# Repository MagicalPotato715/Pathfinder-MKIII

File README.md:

****PATHFINDER: MARK III****

-----

About: This is the PCB for the third generation of my project, Pathfinder. The goal for Pathfinder is to make a hexapod walking robot that is able to traverse in diverse and rugged terrain where conventional vehicles (e.g., cars, rovers) prove inefficient. The third generation of Pathfinder (Mark III) will feature significant upgrades from its predecessor (Mark II), including improved motors for speed and weight-bearing, an onboard 7.4V LiPo battery for tetherless power, an accelerometer, and an NRF chip for wireless communication.

Why: I began Pathfinder after my physics teacher encouraged me to join my school's science fair. I had always had an idea for a spider robot that I kept at the back of my mind, but this pushed me to bring it to life. Over the next few weeks, I poured hours every day into learning more about mechanical and electrical engineering. I also sought mentorship from the UC Berkeley Engineering Department and got connected with a Mech E & EECS graduate student.  Mark I of Pathfinder, a simple prototype/proof of concept, was churned out after 2 weeks, just in time for my district's science fair to win me 2nd place. Mark II was developed a few weeks later for the regional science fair. Mark III, the model this PCB is for, will be the culmination of my work over an entire year to be entered into next season's science fair.

(Note: The CAD model was created and fine-tuned over the course 3+ months that were before Highway began, so I didn't record the process in the journals.)

---

**In Depth: How It Works** (for all yall nerds out there)

- **PCB**
  - The PCB is, in essence, a servo driver. It is supposed to be placed on top of a Nucleo F446RE board, taking advantage of its Morpho pins that expose the MCU. The power comes in from a 7.4V 2S LiPo battery connected to the onboard XT60 (just a connector).
  - **Servos** Since the potential ampage could go up to ~10-15A, a pour is used to connect the battery to the 3 buck converters. Each buck converter steps down the battery power from 7.4V to 6V at 5A for 6 servos (two legs). This connection from the buck converters to the servo rails is led by another set of pours. The servos receive PWM input from 15 pins on the right morpho pins and 3 on the left.
  - **Power** The VIN from the XT60 is also connected to the F446RE's onboard VIN pin (it already has a regulator to step down to 3.3V). This power then comes out of the 3.3V pin and is fed to the NRF Chip and the Accelerometer.
  - **Accelerometer** The accelerometer used is the BNO055, an "INTELLIGENT ABSOLUTE ORIENTATION SENSOR, 9-AXIS SENSOR FUSION" (aka gyroscope & accelerometer and prob 9 other things). The BNO055 uses I2C and is connected to SDA & SCL. There is also a manual reset button connected to RST on the BNO055 just for funsies.
  - **NRF Chip** This is going to be used to communicate with the hand-held controller (to be made later). The NRF Chip is the NRF24L01_Breakout. NRF24L01_Breakout uses SPI and thus the MISO, MOSI, CSN, SCK, and CE pins on the F446RE (used on the left morpho pins).
  
- **Body**
  In-depth desc WIP
---

|Component|Quantity|Model|Lowest Price|Link|
|---|---|---|---|---|
|LED|2|VLMR233T2V2-GS08|$0.35|[Link](https://www.aliexpress.com/item/1005008128628087.html?spm=a2g0o.productlist.main.1.3248724bxQyiaJ&algo_pvid=fe447d84-fd13-4e27-8b43-c86227a91054&algo_exp_id=fe447d84-fd13-4e27-8b43-c86227a91054-0&pdp_ext_f=%7B%22order%22%3A%22-1%22%2C%22eval%22%3A%221%22%7D&pdp_npi=4%40dis%21USD%210.35%210.35%21%21%212.50%212.50%21%40212e520f17525897623118806eb6dd%2112000043902875398%21sea%21TW%216187826129%21ABX&curPageLogUid=l7TbgfaGIsM2&utparam-url=scene%3Asearch%7Cquery_from%3A)|
|Button|2 (1x20pcs)|TL1240NQ1JBLK|$1.27|[Link](https://www.aliexpress.com/item/1005003938985112.html?spm=a2g0o.productlist.main.1.4ec72c6f97uelG&algo_pvid=776e63b0-ad1a-4770-b3bd-8e8a47c59f00&algo_exp_id=776e63b0-ad1a-4770-b3bd-8e8a47c59f00-0&pdp_ext_f=%7B%22order%22%3A%22467%22%2C%22eval%22%3A%221%22%7D&pdp_npi=4%40dis%21USD%212.54%211.27%21%21%212.54%211.27%21%402140f54217525901711175058e53bd%2112000027515313621%21sea%21TW%216187826129%21ABX&curPageLogUid=cPSFccWMC2Xx&utparam-url=scene%3Asearch%7Cquery_from%3A)|
|Servo Motor|18 (2x10pcs)|MG996R|$30.81|[Link](https://www.aliexpress.com/item/1005007032811340.html?spm=a2g0o.productlist.main.1.723942Xa42Xahr&algo_pvid=9b9e645d-9469-4d2a-b561-26204b6bf4cc&algo_exp_id=9b9e645d-9469-4d2a-b561-26204b6bf4cc-0&pdp_ext_f=%7B%22order%22%3A%22876%22%2C%22eval%22%3A%221%22%7D&pdp_npi=4%40dis%21TWD%21150.51%21105.30%21%21%214.96%213.47%21%40212a70c017525889078702858e6fc3%2112000039159590615%21sea%21TW%216187826129%21ABX&curPageLogUid=3yZqtCc75vJ0&utparam-url=scene%3Asearch%7Cquery_from%3A#nav-review)|
|10uF Capacitor|7 (1x100pcs)|0805W106K250CC|$0.6|[Link](https://www.aliexpress.com/item/1626652703.html?spm=a2g0o.productlist.main.1.48fb6316RMeZBk&algo_pvid=e693861e-0391-4f51-8de6-32cd16f941e8&algo_exp_id=e693861e-0391-4f51-8de6-32cd16f941e8-0&pdp_ext_f=%7B%22order%22%3A%22290%22%2C%22eval%22%3A%221%22%7D&pdp_npi=4%40dis%21USD%210.60%210.60%21%21%210.60%210.60%21%402102f22c17525900041745529e7ed1%2165044401121%21sea%21TW%216187826129%21ABX&curPageLogUid=cULtsx9Twjzu&utparam-url=scene%3Asearch%7Cquery_from%3A)|
|10k Resistor|5 (1x100pcs)|CR0805-JW-103ELF|$0.35|[Link](https://www.aliexpress.com/item/1005006269805332.html?spm=a2g0o.productlist.main.1.31e33be6PMcjLK&algo_pvid=54fac39b-245b-4873-a9c8-e36e2fd5a510&algo_exp_id=54fac39b-245b-4873-a9c8-e36e2fd5a510-0&pdp_ext_f=%7B%22order%22%3A%22883%22%2C%22eval%22%3A%221%22%7D&pdp_npi=4%40dis%21USD%210.46%210.35%21%21%213.30%212.51%21%40212e532617525903439675817ef045%2112000036544486825%21sea%21TW%216187826129%21ABX&curPageLogUid=AMuzMQYTT7uu&utparam-url=scene%3Asearch%7Cquery_from%3A)|
|500 Resistor|2 (1x100pcs)|CR0805-FX-4990ELF|$0.35|[Link](https://www.aliexpress.com/item/1005006269805332.html?spm=a2g0o.productlist.main.2.1d257f6fZB1phL&aem_p4p_detail=202507150740589457957524426840000094648&algo_pvid=39ad91cb-3682-4b56-ba16-048ebdbe6b9a&algo_exp_id=39ad91cb-3682-4b56-ba16-048ebdbe6b9a-1&pdp_ext_f=%7B%22order%22%3A%22883%22%2C%22eval%22%3A%221%22%7D&pdp_npi=4%40dis%21USD%210.46%210.35%21%21%213.30%212.51%21%402102f0c917525904583394282ef078%2112000036544486825%21sea%21TW%216187826129%21ABX&curPageLogUid=TxMcy0VHgfnU&utparam-url=scene%3Asearch%7Cquery_from%3A&search_p4p_id=202507150740589457957524426840000094648_1)|
|NRF Board|1|NRF24L01_Breakout|$0.58|[Link](https://www.aliexpress.com/item/1005005642753224.html?spm=a2g0o.productlist.main.5.4aff40c4RsUgXs&algo_pvid=a47926ac-95d7-409f-a2e3-a6df124167e6&algo_exp_id=a47926ac-95d7-409f-a2e3-a6df124167e6-4&pdp_ext_f=%7B%22order%22%3A%22409%22%2C%22eval%22%3A%221%22%7D&pdp_npi=4%40dis%21USD%210.73%210.58%21%21%210.73%210.58%21%40212e532617525905225245131ef08b%2112000033857271479%21sea%21TW%216187826129%21ABX&curPageLogUid=S6MbdsWU3KA5&utparam-url=scene%3Asearch%7Cquery_from%3A)|
|Schottky Resistor|3 (1x20pcs)|MBR1045S|$2.38|[Link](https://www.aliexpress.com/item/3256807600787150.html?spm=a2g0o.productlist.main.1.2124hqbEhqbEzW&algo_pvid=5741d84b-4f22-473b-aa3d-f1e4ee552e5d&algo_exp_id=5741d84b-4f22-473b-aa3d-f1e4ee552e5d-0&pdp_ext_f=%7B%22order%22%3A%2213%22%2C%22eval%22%3A%221%22%7D&pdp_npi=4%40dis%21USD%211.93%211.54%21%21%2113.77%2111.02%21%4021015b7d17526332295795296e3660%2112000042200655705%21sea%21US%216187826129%21ABX&curPageLogUid=Ewd8vUwJ7a2a&utparam-url=scene%3Asearch%7Cquery_from%3A)|
|Buck Converter|3 (1x5pcs)|RT8289GSP|$2.26|[Link](https://www.aliexpress.com/item/1005006319216009.html?spm=a2g0o.productlist.main.1.488d7bbflR8Hqu&algo_pvid=5c03986f-db2c-4932-8ac0-08d611764161&algo_exp_id=5c03986f-db2c-4932-8ac0-08d611764161-0&pdp_ext_f=%7B%22order%22%3A%223%22%2C%22eval%22%3A%221%22%7D&pdp_npi=4%40dis%21USD%212.40%212.26%21%21%2117.10%2116.07%21%402102f0cc17525907096627257e531b%2112000036745251401%21sea%21TW%216187826129%21ABX&curPageLogUid=wGhDPPpYZM8X&utparam-url=scene%3Asearch%7Cquery_from%3A)|
|47uF Capacitor|6 (1x10pcs)|6TAB47M|$10.30|[Link](https://www.aliexpress.com/item/3256807390659102.html?spm=a2g0o.productlist.main.4.3b967067Ham0Q6&algo_pvid=699fcfe8-072e-4534-8b79-86e8dc23af24&algo_exp_id=699fcfe8-072e-4534-8b79-86e8dc23af24-3&pdp_ext_f=%7B%22order%22%3A%221%22%2C%22eval%22%3A%221%22%7D&pdp_npi=4%40dis%21USD%2110.29%213.16%21%21%2173.41%2122.58%21%402141131717526317176228411e5d29%2112000041364017884%21sea%21US%216187826129%21ABX&curPageLogUid=QSGvi9yF7Kbf&utparam-url=scene%3Asearch%7Cquery_from%3A)|
|39k Resistor|3 (1x100pcs)|CR0805-FX-3832ELF|$0.35|[Link](https://www.aliexpress.com/item/1005006269805332.html?spm=a2g0o.productlist.main.1.2d99e8a9Y1xpCE&algo_pvid=5cdcca38-1b66-4097-a40b-18c0ca8f6b01&algo_exp_id=5cdcca38-1b66-4097-a40b-18c0ca8f6b01-0&pdp_ext_f=%7B%22order%22%3A%22883%22%2C%22eval%22%3A%221%22%7D&pdp_npi=4%40dis%21USD%210.46%210.35%21%21%213.30%212.51%21%400b1bf20817525912714461950e34dc%2112000036544486825%21sea%21TW%216187826129%21ABX&curPageLogUid=isIKNlrJEL5x&utparam-url=scene%3Asearch%7Cquery_from%3A)|
|Developement Board|1|Nucleo F446RE|$25.13|[Link](https://www.aliexpress.com/item/3256808854818208.html?spm=a2g0o.productlist.main.5.70b55f227GC5U6&algo_pvid=ffeb3780-3be3-474c-a429-0cbc1474088f&algo_exp_id=ffeb3780-3be3-474c-a429-0cbc1474088f-4&pdp_ext_f=%7B%22order%22%3A%221%22%2C%22eval%22%3A%221%22%7D&pdp_npi=4%40dis%21USD%2125.13%2125.13%21%21%21179.23%21179.23%21%4021010d9017526322255465060e5ffc%2112000047682286878%21sea%21US%216187826129%21ABX&curPageLogUid=D5Uxs2NBLRa4&utparam-url=scene%3Asearch%7Cquery_from%3A)|
|10uH Inductor|3 (1x10pcs)|EXL1V0505-100-R|$2.43|[Link](https://www.aliexpress.com/item/1005007254030376.html?spm=a2g0o.productlist.main.2.307049c0X6dLSL&aem_p4p_detail=202507151745373616657531123840000673656&algo_pvid=66b3ed77-bee8-4268-b83d-4e92fd2fc043&algo_exp_id=66b3ed77-bee8-4268-b83d-4e92fd2fc043-1&pdp_ext_f=%7B%22order%22%3A%2294%22%2C%22eval%22%3A%221%22%7D&pdp_npi=4%40dis%21USD%212.06%211.92%21%21%2114.68%2113.65%21%402102f0cc17526267373823299e52ca%2112000039958467830%21sea%21TW%216187826129%21ABX&curPageLogUid=8Wouj4IIFV9r&utparam-url=scene%3Asearch%7Cquery_from%3A&search_p4p_id=202507151745373616657531123840000673656_1)|
|XT60 Connector|1|XT60-M|$0.39|[Link](https://www.aliexpress.com/item/1005007103438736.html?spm=a2g0o.productlist.main.3.1de71f01UKNinh&algo_pvid=95e61be6-b3b9-4538-b7d2-54140ca63c98&algo_exp_id=95e61be6-b3b9-4538-b7d2-54140ca63c98-2&pdp_ext_f=%7B%22order%22%3A%226969%22%2C%22eval%22%3A%221%22%7D&pdp_npi=4%40dis%21USD%210.62%210.39%21%21%214.41%212.78%21%402140ed7717526289941694832e776d%2112000039413700479%21sea%21TW%216187826129%21ABX&curPageLogUid=F0xwn0UJwDcT&utparam-url=scene%3Asearch%7Cquery_from%3A)|
|Battery|1|7.4v 2s Lipo|$29.49|[Link](https://www.aliexpress.com/item/3256802810308498.html?spm=a2g0o.productlist.main.10.1419692ehL6tSZ&aem_p4p_detail=202507151859467433250087118600000828398&algo_pvid=65a93eab-ee7e-4be5-ab04-d89be2b2ebf3&algo_exp_id=65a93eab-ee7e-4be5-ab04-d89be2b2ebf3-9&pdp_ext_f=%7B%22order%22%3A%2262%22%2C%22eval%22%3A%221%22%7D&pdp_npi=4%40dis%21USD%2149.98%2129.49%21%21%2149.98%2129.49%21%40212e508d17526311863668524e73a1%2112000028180190182%21sea%21US%216187826129%21ABX&curPageLogUid=LakY9sldwBu8&utparam-url=scene%3Asearch%7Cquery_from%3A&search_p4p_id=202507151859467433250087118600000828398_3)|
|0.1uF Capacitor|3 (1x100pcs)|0603B104K250SD|$0.95|[Link](https://www.aliexpress.com/item/1005003512666695.html?spm=a2g0o.productlist.main.2.bb674964zgo3zW&aem_p4p_detail=202507151825544677393916540000689187&algo_pvid=30290dc5-6cab-4384-9250-c0f4dd7da1ce&algo_exp_id=30290dc5-6cab-4384-9250-c0f4dd7da1ce-1&pdp_ext_f=%7B%22order%22%3A%2266%22%2C%22eval%22%3A%221%22%7D&pdp_npi=4%40dis%21USD%210.95%210.95%21%21%210.95%210.95%21%400b1bf20a17526291538932348e9ac6%2112000026122537038%21sea%21TW%216187826129%21ABX&curPageLogUid=3zYrgz8WWygI&utparam-url=scene%3Asearch%7Cquery_from%3A&search_p4p_id=202507151825544677393916540000689187_1)|
|Accelerometer|1|BNO055|$29.32|[Link](https://www.aliexpress.com/item/3256809169239048.html?spm=a2g0o.productlist.main.4.3bcb1ccf4PvH8r&algo_pvid=e7c705af-71c5-41ca-b796-970d70bc8c14&algo_exp_id=e7c705af-71c5-41ca-b796-970d70bc8c14-3&pdp_ext_f=%7B%22order%22%3A%222%22%2C%22eval%22%3A%221%22%7D&pdp_npi=4%40dis%21USD%2131.19%2129.32%21%21%21222.46%21209.11%21%40214100f417526315452977374e76fc%2112000048851091864%21sea%21US%216187826129%21ABX&curPageLogUid=vcOzWTYEZgSK&utparam-url=scene%3Asearch%7Cquery_from%3A)|
|Female Headers|2 (1x10pcs)|PPPC192LFBN-RC|$0.89|[Link](https://www.aliexpress.com/item/4001198421663.html?spm=a2g0o.productlist.main.1.53b448ed3nbjvM&algo_pvid=b77199fa-d225-4b06-920e-1e9f2247e7c7&algo_exp_id=b77199fa-d225-4b06-920e-1e9f2247e7c7-0&pdp_ext_f=%7B%22order%22%3A%223754%22%2C%22eval%22%3A%221%22%7D&pdp_npi=4%40dis%21USD%210.56%210.48%21%21%210.56%210.48%21%402140f53817526293708992891e4ad8%2110000015275671639%21sea%21TW%216187826129%21ABX&curPageLogUid=mkUieaDajPN6&utparam-url=scene%3Asearch%7Cquery_from%3A)|
|Male Headers|18 (1x50pcs)|TS-103-G-A|$0.94|[Link](https://www.aliexpress.com/item/4000988113226.html?spm=a2g0o.productlist.main.4.3e7d225ff81nTC&algo_pvid=fa0decd7-7944-4609-9363-1b7ce34f160f&algo_exp_id=fa0decd7-7944-4609-9363-1b7ce34f160f-3&pdp_ext_f=%7B%22order%22%3A%221703%22%2C%22eval%22%3A%221%22%7D&pdp_npi=4%40dis%21USD%211.25%210.94%21%21%211.25%210.94%21%40212a6e2917526295363814312e0834%2110000013202368860%21sea%21TW%216187826129%21ABX&curPageLogUid=NrD7a47zgcIJ&utparam-url=scene%3Asearch%7Cquery_from%3A)|
|PCB Board|1| |$76.88|JLCPCB Order|

Total Components Price (+26.63 Shipping & tax): $223.39
PCB Price: $76.88
Total Price: $280.27

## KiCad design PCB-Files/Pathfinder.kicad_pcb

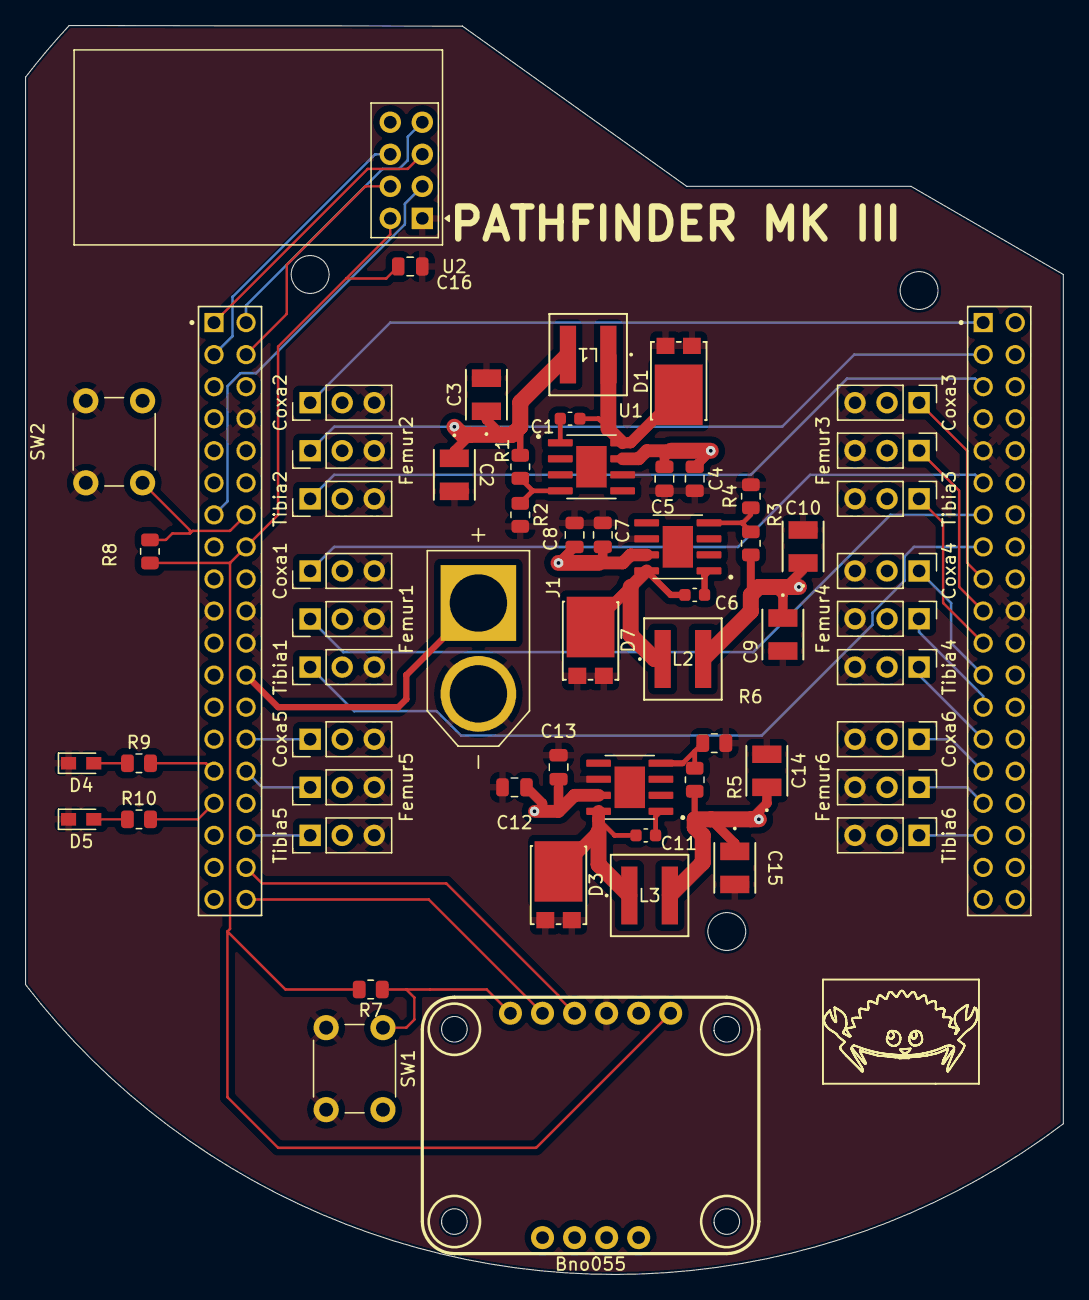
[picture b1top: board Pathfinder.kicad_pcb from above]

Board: 4 copper layers, 82.2 x 99.0 mm, 61 parts (0 on the bottom side), 46 nets.

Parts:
Bno055: BNO055
BuckConverterA1: SOIC127P599X175-9N
BuckConverterB1: SOIC127P599X175-9N
BuckConverterC1: SOIC127P599X175-9N
C1, C6, C11: 0.1uF; C_0603_1608Metric
C2, C3, C9, C10, C14, C15: 47uF; CAP_TA_B2_PAN
C4, C5, C7, C8, C12, C13, C16: 10uF; C_0805_2012Metric
Coxa1, Coxa2, Coxa3, Coxa4, Coxa5, Coxa6: Motor_Servo; PinHeader_1x03_P2.54mm_Vertical
D1, D3, D7: D_Schottky; MBR1045S
D4, D5: LED; LED_miniPLCC_2315_Handsoldering
Femur1, Femur2, Femur3, Femur4, Femur5, Femur6: Motor_Servo; PinHeader_1x03_P2.54mm_Vertical
J1: XT60-M; AMASS_XT60-M
L1, L2, L3: 10uH; IND_EXL1V0505-100-R_COB
R1, R3, R5: 38k; R_0805_2012Metric
R2, R4, R6, R7, R8: 10k; R_0805_2012Metric
R9, R10: 500; R_0805_2012Metric
SW1, SW2: SW_Push; SW_PUSH_6mm_H9.5mm
Tibia1, Tibia2, Tibia3, Tibia4, Tibia5, Tibia6: Motor_Servo; PinHeader_1x03_P2.54mm_Vertical
U1: NUCLEO-F446RE; MODULE_NUCLEO-F446RE
U2: NRF24L01_Breakout; nRF24L01_Breakout

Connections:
+3.3V: Bno055.Vin, C16.1, R7.2, R8.2, U1.CN7_16 (CN7_+3V3), U2.2 (VCC)
+6VA: C2.1, C3.1, Coxa1.2 (+), Coxa2.2 (+), Femur1.2 (+), Femur2.2 (+), L1.2, R1.1, Tibia1.2 (+), Tibia2.2 (+)
+6VB: C9.1, C10.1, Coxa3.2 (+), Coxa4.2 (+), Femur3.2 (+), Femur4.2 (+), L2.2, R3.1, Tibia3.2 (+), Tibia4.2 (+)
+6VC: C14.1, C15.1, Coxa5.2 (+), Coxa6.2 (+), Femur5.2 (+), Femur6.2 (+), L3.2, R5.1, Tibia5.2 (+), Tibia6.2 (+)
+BATT: BuckConverterA1.7 (VIN), BuckConverterB1.7 (VIN), BuckConverterC1.7 (VIN), C4.1, C5.1, C7.1, C8.1, C12.1, C13.1, J1.P (POS), U1.CN7_24 (CN7_VIN)
/CE: U1.CN7_13 (PA13), U2.3 (CE)
/CSN: U1.CN7_4 (PD2), U2.4 (~CSN)
/MISO: U1.CN7_2 (PC11), U2.7 (MISO)
/MOSI: U1.CN7_3 (PC12), U2.6 (MOSI)
/PA_0: Coxa5.1 (PWM), U1.CN7_28 (PA0)
/PA_1: Femur5.1 (PWM), U1.CN7_30 (PA1)
/PA_5: Coxa1.1 (PWM), U1.CN10_11 (PA5)
/PA_6: Femur1.1 (PWM), U1.CN10_13 (PA6)
/PA_7: Tibia1.1 (PWM), U1.CN10_15 (PA7)
/PA_8: Coxa4.1 (PWM), U1.CN10_23 (PA8)
/PA_9: Tibia3.1 (PWM), U1.CN10_21 (PA9)
/PA_10: Tibia6.1 (PWM), U1.CN10_33 (PA10)
/PB_0: Tibia5.1 (PWM), U1.CN7_34 (PB0)
/PB_3: Femur6.1 (PWM), U1.CN10_31 (PB3)
/PB_4: Tibia4.1 (PWM), U1.CN10_27 (PB4)
/PB_5: Coxa6.1 (PWM), U1.CN10_29 (PB5)
/PB_6: Coxa3.1 (PWM), U1.CN10_17 (PB6)
/PB_8: Femur2.1 (PWM), U1.CN10_3 (PB8)
/PB_9: Tibia2.1 (PWM), U1.CN10_5 (PB9)
/PB_10: Femur4.1 (PWM), U1.CN10_25 (PB10)
/PC_7: Femur3.1 (PWM), U1.CN10_19 (PC7)
/PC_9: Coxa2.1 (PWM), U1.CN10_1 (PC9)
/PH_0: R9.2, U1.CN7_29 (PH0)
/PH_1: R10.2, U1.CN7_31 (PH1)
/SCK: U1.CN7_1 (PC10), U2.5 (SCK)
/SCL: Bno055.SCL, U1.CN7_38 (PC0/PB8)
/SDA: Bno055.SDA, U1.CN7_36 (PC1/PB9)
GND: Bno055.GND, BuckConverterA1.6 (GND), BuckConverterB1.6 (GND), BuckConverterC1.6 (GND), C2.2, C3.2, C4.2, C5.2, C7.2, C8.2, C9.2, C10.2, C12.2, C13.2, C14.2, C15.2, C16.2, Coxa1.3 (-), Coxa2.3 (-), Coxa3.3 (-), Coxa4.3 (-), Coxa5.3 (-), Coxa6.3 (-), D1.1 (A), D1.3 (A), D3.1 (A), D3.3 (A), D4.1 (K), D5.1 (K), D7.1 (A), D7.3 (A), Femur1.3 (-), Femur2.3 (-), Femur3.3 (-), Femur4.3 (-), Femur5.3 (-), Femur6.3 (-), J1.N (NEG), R2.2, R4.2, R6.2, SW1.2, SW2.2, Tibia1.3 (-), Tibia2.3 (-), Tibia3.3 (-), Tibia4.3 (-), Tibia5.3 (-), Tibia6.3 (-), U1.CN7_8 (CN7_GND), U1.CN7_19 (CN7_GND), U1.CN7_20 (CN7_GND), U1.CN7_22 (CN7_GND), U1.CN10_9 (CN10_GND), U1.CN10_20 (CN10_GND), U2.1 (GND)
unnamed: Bno055.RST, R7.1, SW1.1
unnamed: BuckConverterA1.1 (Boot), C1.1
unnamed: BuckConverterA1.4 (FB), R1.2, R2.1
unnamed: BuckConverterA1.8 (SW), C1.2, D1.2 (K), L1.1
unnamed: BuckConverterB1.1 (Boot), C6.1
unnamed: BuckConverterB1.4 (FB), R3.2, R4.1
unnamed: BuckConverterB1.8 (SW), C6.2, D7.2 (K), L2.1
unnamed: BuckConverterC1.1 (Boot), C11.1
unnamed: BuckConverterC1.4 (FB), R5.2, R6.1
unnamed: BuckConverterC1.8 (SW), C11.2, D3.2 (K), L3.1
unnamed: D4.2 (A), R9.1
unnamed: D5.2 (A), R10.1
unnamed: R8.1, SW2.1, U1.CN7_14 (CN7_RESET)

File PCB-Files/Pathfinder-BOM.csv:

"Id";"Designator";"Footprint";"Quantity";"Designation";"Supplier and ref";
1;"D4,D5";"LED_miniPLCC_2315_Handsoldering";2;"LED";;;
2;"SW2,SW1";"SW_PUSH_6mm_H9.5mm";2;"SW_Push";;;
3;"Coxa2,Femur1,Tibia5,Tibia1,Femur3,Coxa4,Coxa5,Tibia3,Tibia2,Coxa3,Femur6,Femur4,Tibia4,Coxa6,Coxa1,Tibia6,Femur5,Femur2";"PinHeader_1x03_P2.54mm_Vertical";18;"Motor_Servo";;;
4;"C8,C5,C7,C13,C16,C4,C12";"C_0805_2012Metric";7;"10uF";;;
5;"R7,R6,R4,R8,R2";"R_0805_2012Metric";5;"10k";;;
6;"R9,R10";"R_0805_2012Metric";2;"500";;;
7;"U2";"nRF24L01_Breakout";1;"NRF24L01_Breakout";;;
8;"D7,D1,D3";"MBR1045S";3;"D_Schottky";;;
9;"BuckConverterB1,BuckConverterC1,BuckConverterA1";"SOIC127P599X175-9N";3;"~";;;
10;"C2,C3,C9,C15,C10,C14";"CAP_TA_B2_PAN";6;"47uF";;;
11;"R5,R1,R3";"R_0805_2012Metric";3;"38k";;;
12;"U1";"MODULE_NUCLEO-F446RE";1;"NUCLEO-F446RE";;;
13;"L3,L1,L2";"IND_EXL1V0505-100-R_COB";3;"10uH";;;
14;"J1";"AMASS_XT60-M";1;"XT60-M";;;
15;"C11,C6,C1";"C_0603_1608Metric";3;"0.1uF";;;
16;"Bno055";"BNO055";1;"~";;;

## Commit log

2025-07-07 Rename PFinder.zip to Pathfinder-Gerber.zip
2025-07-07 Rename Pathfinder 2.zip to Pathfinder-Project_Files.zip
2025-07-08 Rename Pathfinder 3.zip to Pathfinder-Project_Files.zip
2025-07-08 Rename PFinder.zip to Pathfinder-Gerbers.zip
2025-07-09 Create Test
2025-07-09 Create remove me
2025-07-09 Rename Pathfinder.pdf to Schematic.pdf
2025-07-15 Create Hugh
2025-07-15 Rename Hugh to Theres nothing wrong with my file names
2025-07-18 Create ...
2025-07-18 Create h
2025-07-18 Create j
